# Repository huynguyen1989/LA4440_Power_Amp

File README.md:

# LA4440_Power_Amp
- Power amplifier based on LA4440 Module
- This reposistory contain final development of LA4440 Module to board out version 2 Mono channel following its datasheet

- Mono Channel each board and providing 19W per channel in Bridge Mode
- Single Power Supply from 18Vdc to 25Vdc within surge voltage 50Vdc < 0.2s

- Panelized version within Kikit placed at the Panelized folder -> 10 board per A4 size for PCB manufacturing
## KiCAD
- Version 7.x
## Assets
- Assets folder contain PDFs and Images of the module PCB

## Libraries
- Components and Libraries come within

### Single Board

### 10 Board using Kikit

# License
Free to use

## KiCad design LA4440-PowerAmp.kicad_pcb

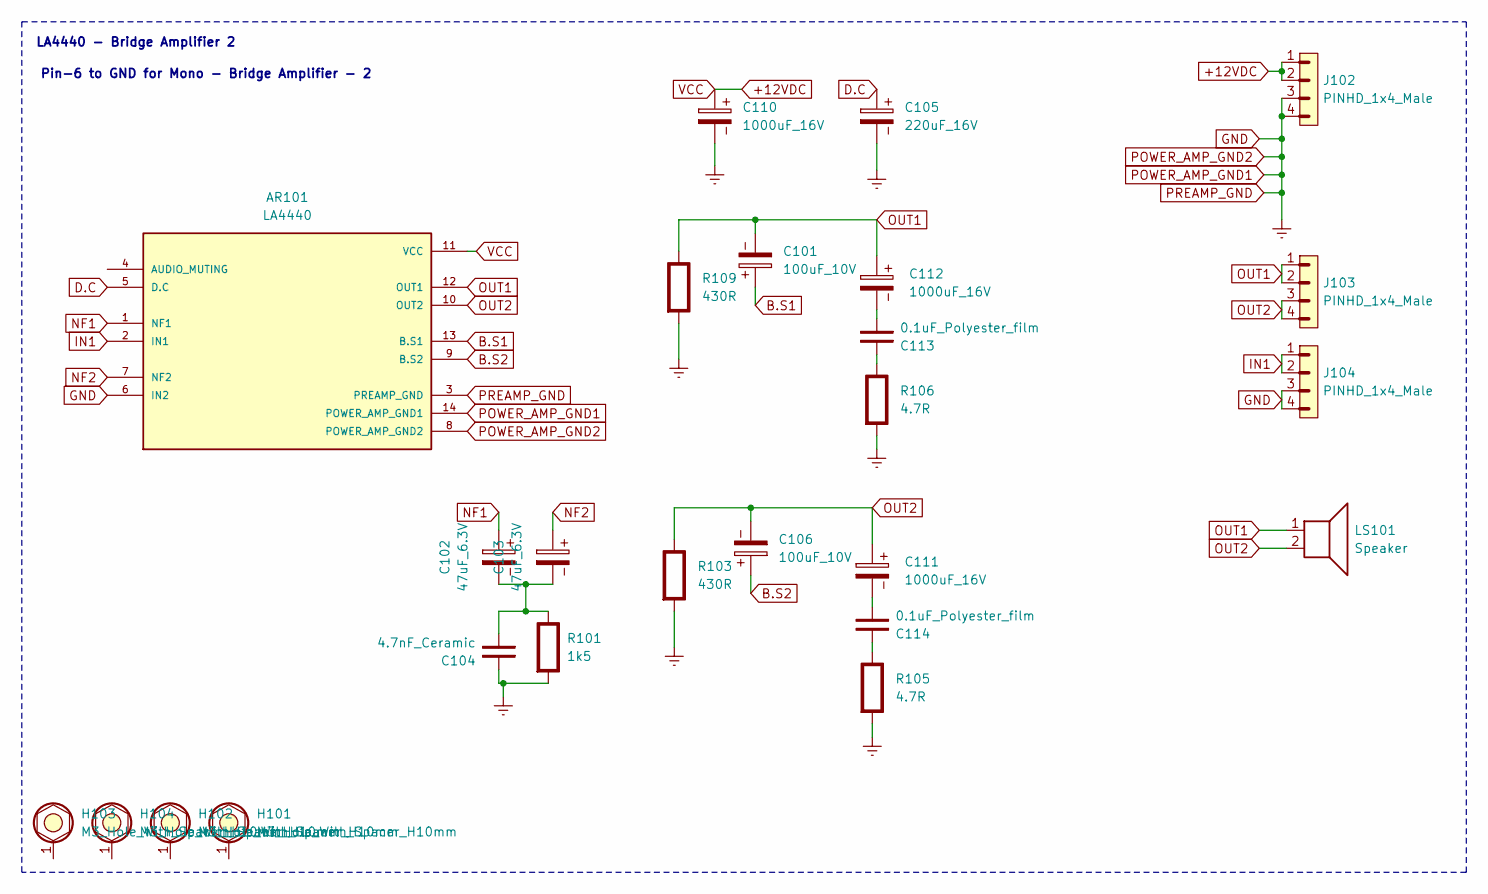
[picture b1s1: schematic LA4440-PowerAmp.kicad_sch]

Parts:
AR101: LA4440; PARTREV 23 Oct 2013
C101, C106: 100uF_10V; CP_Radial_D5.0mm_P2.00mm
C102, C103: 47uF_6.3V; CP_Radial_D4.0mm_P1.50mm
C104: 4.7nF_Ceramic; C_Disc_D5.0mm_W2.5mm_P2.50mm
C105: 220uF_16V; CP_Radial_D8.0mm_P3.50mm
C110, C111, C112: 1000uF_16V; CP_Radial_D10.0mm_P5.00mm
C113, C114: 0.1uF_Polyester_film; C_Disc_D5.0mm_W2.5mm_P2.50mm
H101, H102, H103, H104: M3_Hole_With_Spacer_H10mm; MountingHole_3.2mm_With_Spacer_H10mm
J102, J103, J104: PINHD_1x4_Male; PinHeader_1x04_P2.54mm_Vertical
LS101: Speaker
R101: 1k5; R_Axial_DIN0204_L3.6mm_D1.6mm_P7.62mm_Horizontal; Rating W
R103, R109: 430R; R_Axial_DIN0204_L3.6mm_D1.6mm_P7.62mm_Horizontal; Rating W
R105, R106: 4.7R; R_Axial_DIN0204_L3.6mm_D1.6mm_P7.62mm_Horizontal; Rating W

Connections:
+12VDC: AR101.11 (VCC), C110.1, J102.1, J102.2
B.S1: AR101.13 (B.S1), C101.1
B.S2: AR101.9 (B.S2), C106.1
D.C: AR101.5 (D.C), C105.1
GND: AR101.3 (PREAMP_GND), AR101.6 (IN2), AR101.8 (POWER_AMP_GND2), AR101.14 (POWER_AMP_GND1), C104.2, C105.2, C110.2, J102.3, J102.4, J104.3, J104.4, R101.2 (-), R103.2 (-), R105.2 (-), R106.2 (-), R109.2 (-)
IN1: AR101.2 (IN1), J104.1, J104.2
NF1: AR101.1 (NF1), C102.1
NF2: AR101.7 (NF2), C103.1
unnamed: C111.2, C114.1
unnamed: C112.2, C113.1
unnamed: C102.2, C103.2, C104.1, R101.1 (+)
unnamed: C114.2, R105.1 (+)
unnamed: C113.2, R106.1 (+)
OUT1: AR101.12 (OUT1), C101.2, C112.1, J103.1, J103.2, LS101.1, R109.1 (+)
OUT2: AR101.10 (OUT2), C106.2, C111.1, J103.3, J103.4, LS101.2, R103.1 (+)

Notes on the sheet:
Pin-6 to GND for Mono - Bridge Amplifier - 2
LA4440 - Bridge Amplifier 2

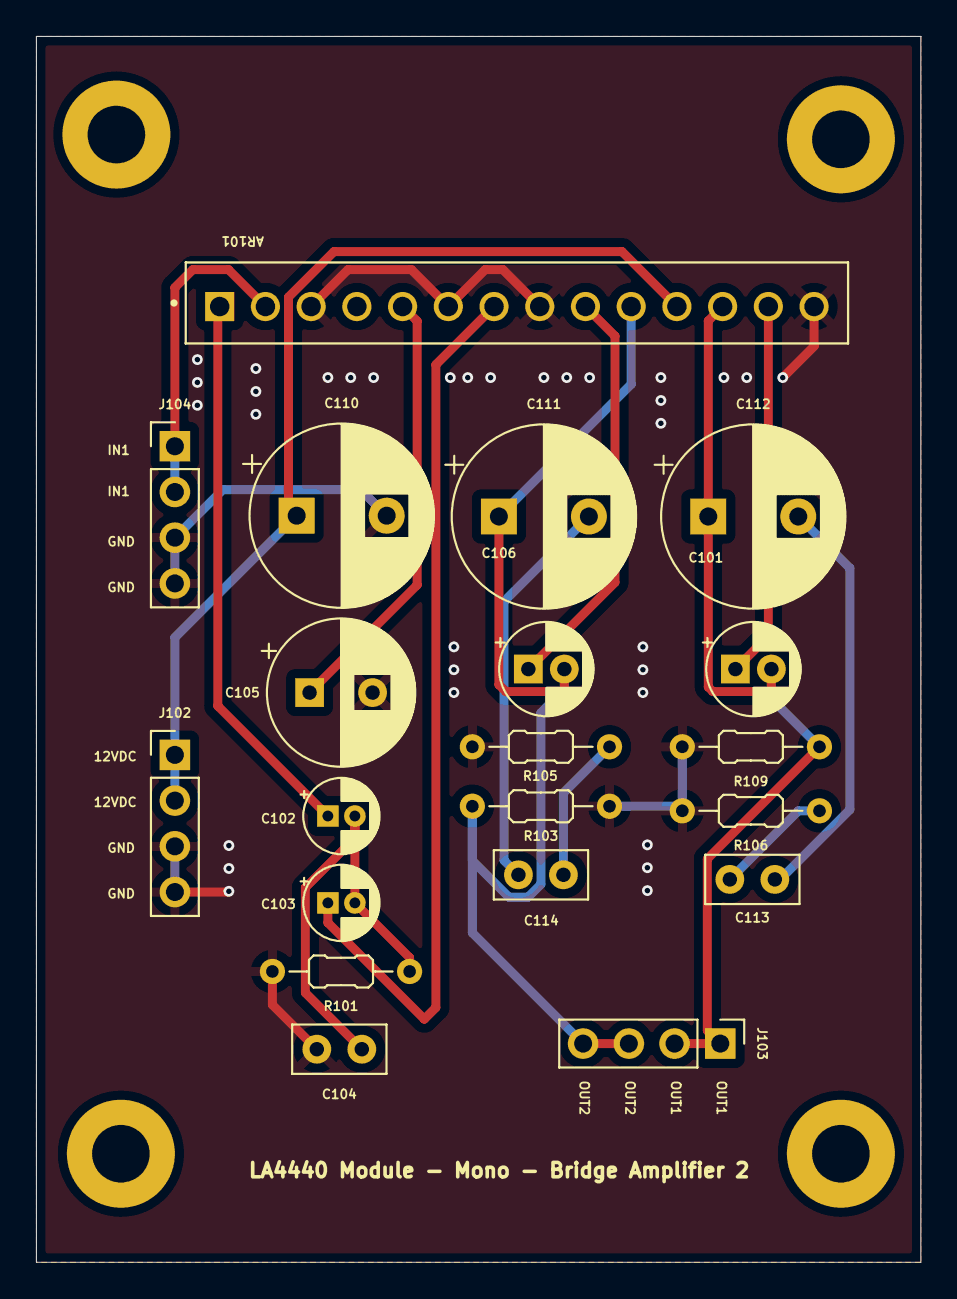
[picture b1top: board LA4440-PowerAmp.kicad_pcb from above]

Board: 2 copper layers, 49.1 x 68.1 mm, 24 parts (0 on the bottom side), 15 nets.

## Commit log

2024-10-28 Init
2024-10-28 Add Assets
2024-10-28 Add Images
2024-10-28 Add Kicad Version
